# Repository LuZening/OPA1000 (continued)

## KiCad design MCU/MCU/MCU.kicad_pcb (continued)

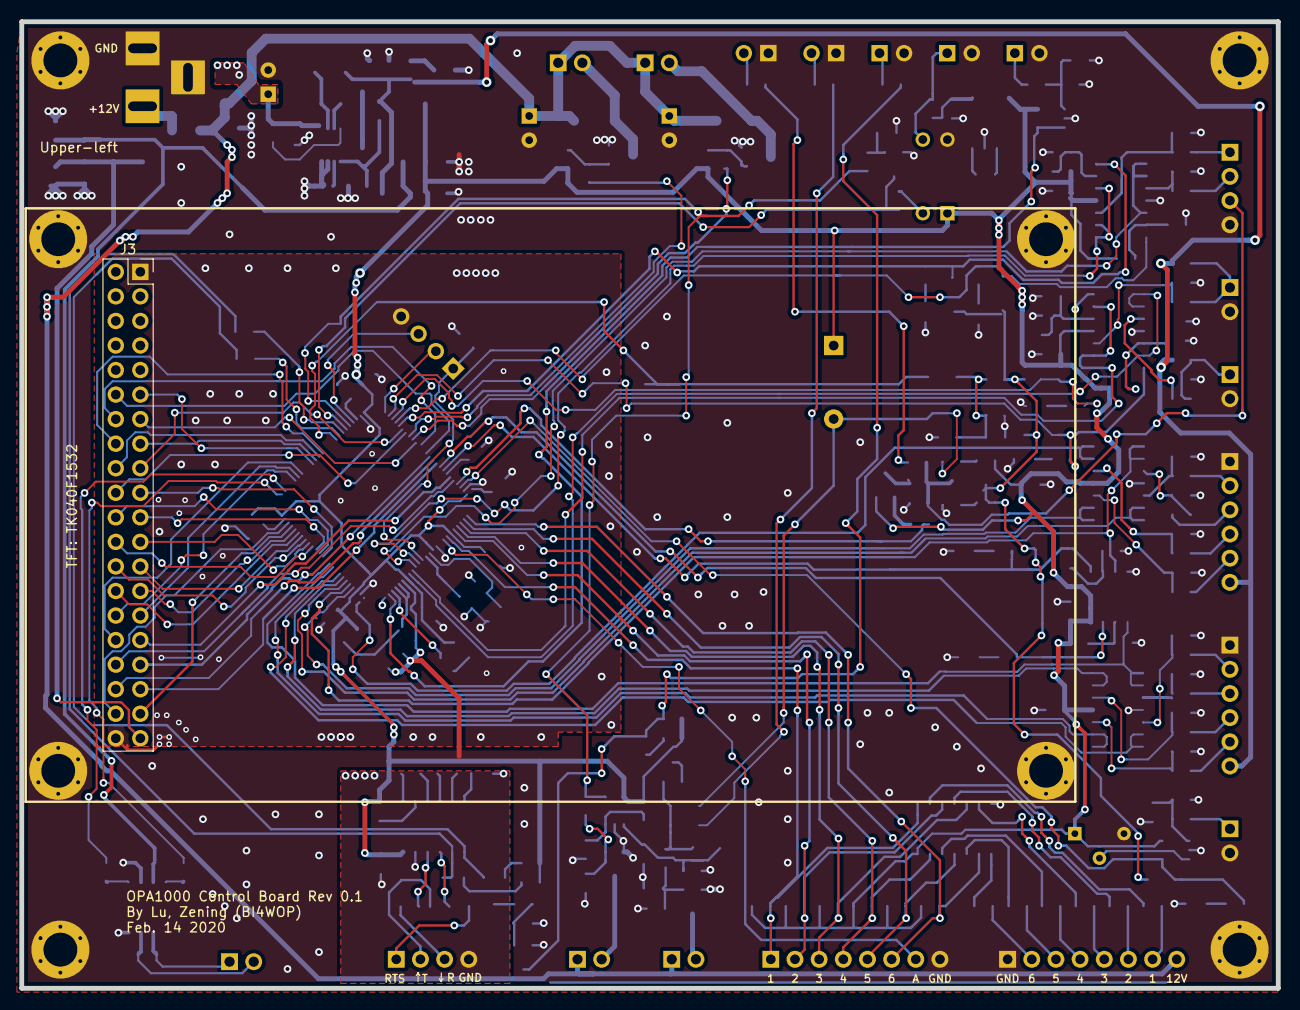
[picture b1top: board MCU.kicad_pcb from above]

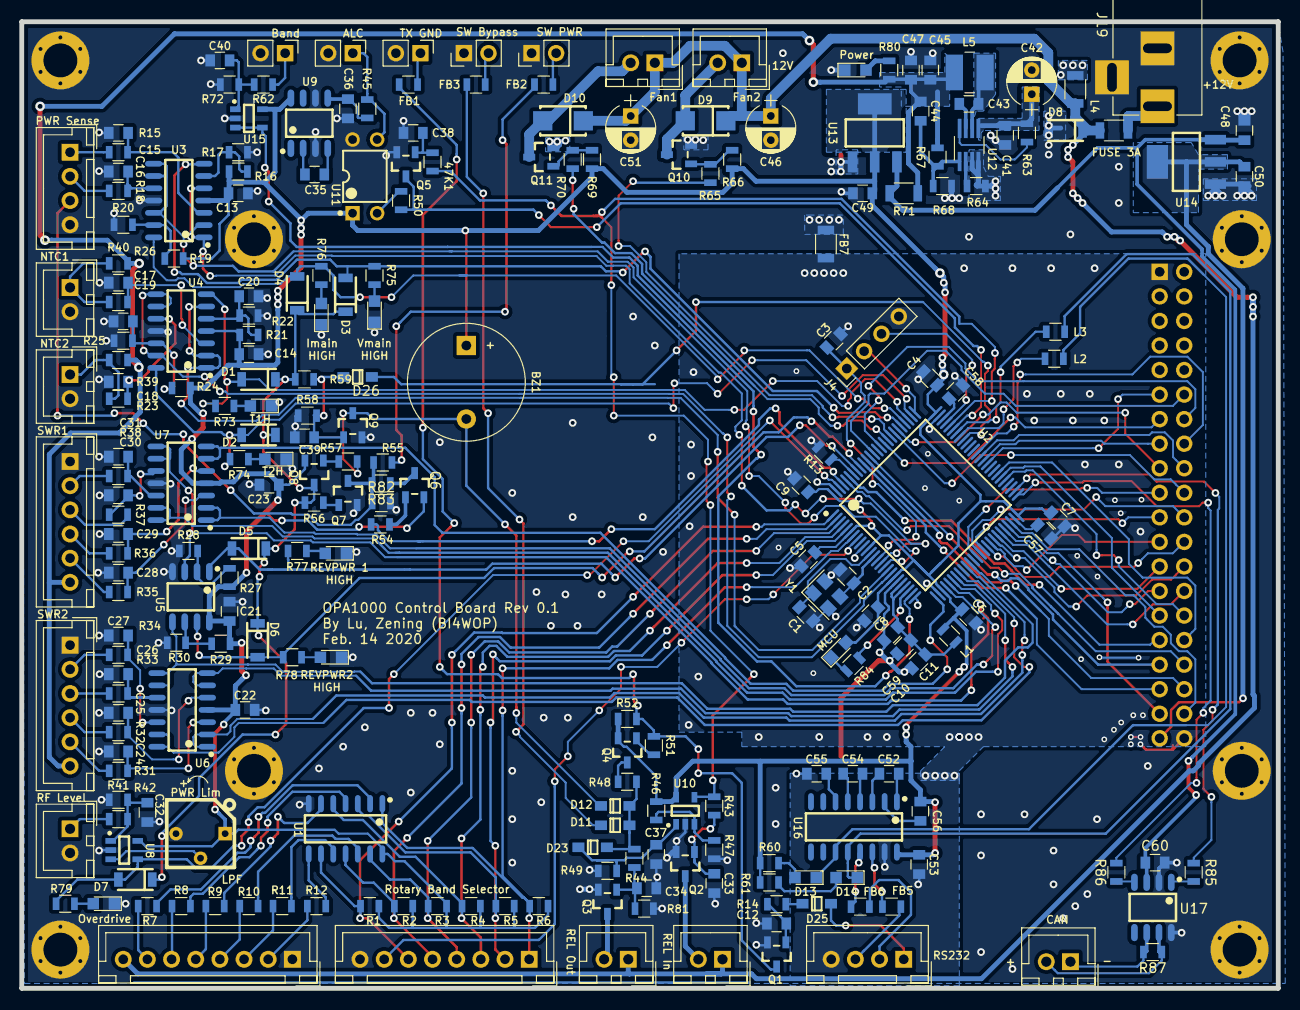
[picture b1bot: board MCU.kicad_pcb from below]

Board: 2 copper layers, 130.0 x 100.0 mm, 246 parts (237 on the bottom side), 199 nets.

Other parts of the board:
47K1: R_Small; R_0805
D26: SD103; SOD-123

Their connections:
/FaultHandling/Clear_Fault: D26.1; also elsewhere on the board
Clear_fault: D26.2; also elsewhere on the board
unnamed 86: 47K1.1; also elsewhere on the board
Transmit: 47K1.2; also elsewhere on the board

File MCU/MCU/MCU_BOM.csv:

"Comment","Description","Designator","Footprint","LibRef","Pins","Quantity","PartNumber","url",
"C_Small","desc","C34,C33,C23,C22,C21,C2,C1,","C_0805","libref","2","7","","",
"1nF","desc","C38,","C_0805","libref","2","1","","",
"102","desc","C39,","C_0805","libref","2","1","","",
"10nF NP0","desc","C43,","C_0805","libref","2","1","","",
"47pF","desc","C44,","C_0805","libref","2","1","","",
"10uF","desc","C50,C49,C45,C37,C36,C35,C11,","C_0805","libref","2","7","","",
"104","desc","C60,C59,C58,C57,C56,C55,C54,C53,C52,C48,C47,C41,C40,C32,C31,C30,C29,C28,C27,C26,C25,C24,C20,C19,C18,C17,C16,C15,C14,C13,C12,C10,C9,C8,C7,C6,C5,C4,C3,","C_0805","libref","2","39","","",
"SS14","desc","D10,D9,","SMA(DO-214AC)_S1","libref","2","2","","",
"T1H","desc","D15,","LED_0805","libref","2","1","","",
"T2H","desc","D16,","LED_0805","libref","2","1","","",
"VmH","desc","D17,","LED_0805","libref","2","1","","",
"ImH","desc","D18,","LED_0805","libref","2","1","","",
"R1H","desc","D19,","LED_0805","libref","2","1","","",
"R2H","desc","D20,","LED_0805","libref","2","1","","",
"OD","desc","D21,","LED_0805","libref","2","1","","",
"Power","desc","D22,","LED_0805","libref","2","1","","",
"LED","desc","D24,D14,D13,","LED_0805","libref","2","3","","",
"SD103","desc","D26,D25,D23,D12,D11,","SOD-123","libref","2","5","","",
"D","desc","D7,D6,D5,D4,D3,D2,D1,","LL-34","libref","2","7","","",
"16V","desc","D8,","LL-34","libref","2","1","","",
"2A","desc","F1,","R_1206","libref","2","1","","",
"1K","desc","FB6,FB5,FB3,FB2,FB1,R72,R61,R60,R58,R54,R44,R43,R41,R40,R39,R38,R37,R36,R35,R34,R33,R32,R31,R30,R29,R28,R27,R26,R25,R24,R23,R22,R21,R20,R19,R18,R17,R16,R15,","R_0805","libref","2","39","","",
"1K","desc","FB7,","R_1206","libref","2","1","","",
"600Ohm","desc","L3,L2,L1,","L_0805","libref","2","3","","",
"BEAD","desc","L4,","L_1206","libref","2","1","","",
"22uH","desc","L5,","L_SMD4030_hand","libref","2","1","","",
"AO3402","desc","Q11,Q10,","SOT-23(SOT-23-3)","libref","3","2","","",
"8550","desc","Q6,Q8,Q4,","SOT-23(SOT-23-3)","libref","3","3","","",
"8050","desc","Q9,Q7,Q5,Q3,Q2,Q1,","SOT-23(SOT-23-3)","libref","3","6","","",
"22K","desc","R42,","R_0805","libref","2","1","","",
"33k","desc","R46,","R_0805","libref","2","1","","",
"68K","desc","R47,","R_0805","libref","2","1","","",
"47K","desc","R51,","R_0805","libref","2","1","","",
"10","desc","R55,","R_0805","libref","2","1","","",
"3.3K","desc","R59,","R_0805","libref","2","1","","",
"100K","desc","R67,R64,R63,R57,R52,","R_0805","libref","2","5","","",
"16K","desc","R68,","R_0805","libref","2","1","","",
"0","desc","R71,","R_1206","libref","2","1","","",
"2.2K","desc","R80,R79,R78,R77,R76,R75,R74,R73,R50,","R_0805","libref","2","9","","",
"R_Small","desc","R81,47K1,","R_0805","libref","2","2","","",
"10K","desc","R83,R82,R69,R66,R56,R49,R48,R14,R6,R5,R4,R3,R2,R1,","R_0805","libref","2","14","","",
"4.7K","desc","R84,R45,R13,R12,R11,R10,R9,R8,R7,","R_0805","libref","2","9","","",
"100","desc","R86,R85,R70,R65,R62,","R_0805","libref","2","5","","",
"120","desc","R87,","R_0805","libref","2","1","","",
"74HC04","desc","U1,","SOIC-14_150MIL","libref","14","1","","",
"SY8303","desc","U12,","TSOT-23-8_HandSoldering","libref","8","1","","",
"AZ1117-3.3","desc","U14,U13,","SOT-223","libref","4","2","","",
"LMV321","desc","U15,U10,U8,","SOT-23-5","libref","5","3","","",
"MAX3232","desc","U16,","SOIC-16_150MIL","libref","16","1","","",
"TJA1042T","desc","U17,","SOIC-8_150MIL","libref","8","1","","",
"STM32F407VETx","desc","U2,","LQFP-100_14X14X05P","libref","100","1","","",
"LMV358","desc","U5,","SOIC-8_150MIL","libref","8","1","","",
"LMV324","desc","U6,U4,U7,U3,","SOIC-14_150MIL","libref","14","4","","",
"ICL7660","desc","U9,","SOIC-8_150MIL","libref","8","1","","",
"12MHz","desc","Y1,","Crystal_SMD_3225-4pin_3.2x2.5mm","libref","4","1","","",
"Through Hole Items ",
"Conn_02x20_Odd_Even","desc","J3,","Socket_Strip_Straight_2x20_Pitch2.54mm","libref","40","1","","",
"GND","desc","SC8,SC7,SC6,SC5,SC4,SC3,SC2,SC1,","M3_Screwhole","libref","7","8","","",
"Buzzer","desc","BZ1,","Buzzer_12x9.5RM7.6","libref","2","1","","",
"10u","desc","C42,","CP_Radial_D5.0mm_P2.50mm","libref","2","1","","",
"25V 47uF","desc","C51,C46,","CP_Radial_D5.0mm_P2.50mm","libref","2","2","","",
"Conn_01x02","desc","J11,J12,J10,J7,J6,","JST_XH_B02B-XH-A_02x2.50mm_Straight","libref","2","5","","",
"Conn_01x02","desc","J15,J13,J18,J16,J14,","Pin_Header_Straight_1x02_Pitch2.54mm","libref","2","5","","",
"Conn_01x04","desc","J17,J5,","JST_XH_B04B-XH-A_04x2.50mm_Straight","libref","4","2","","",
"Barrel_Jack_Switch","desc","J19,","BARREL_JACK","libref","3","1","","",
"Conn_01x08","desc","J2,J1,","JST_XH_B08B-XH-A_08x2.50mm_Straight","libref","8","2","","",
"CAN","desc","J20,","JST_XH_B02B-XH-A_02x2.50mm_Straight","libref","2","1","","",
"Conn_01x04","desc","J4,","Pin_Header_Straight_1x04_Pitch2.54mm","libref","4","1","","",
"Conn_01x06","desc","J9,J8,","JST_XH_B06B-XH-A_06x2.50mm_Straight","libref","6","2","","",
"Fan","desc","M2,M1,","JST_XH_B02B-XH-A_02x2.50mm_Straight","libref","2","2","","",
"10K","desc","RV1,","3362P","libref","3","1","","",
"PC817","desc","U11,","DIP-4","libref","4","1","","",

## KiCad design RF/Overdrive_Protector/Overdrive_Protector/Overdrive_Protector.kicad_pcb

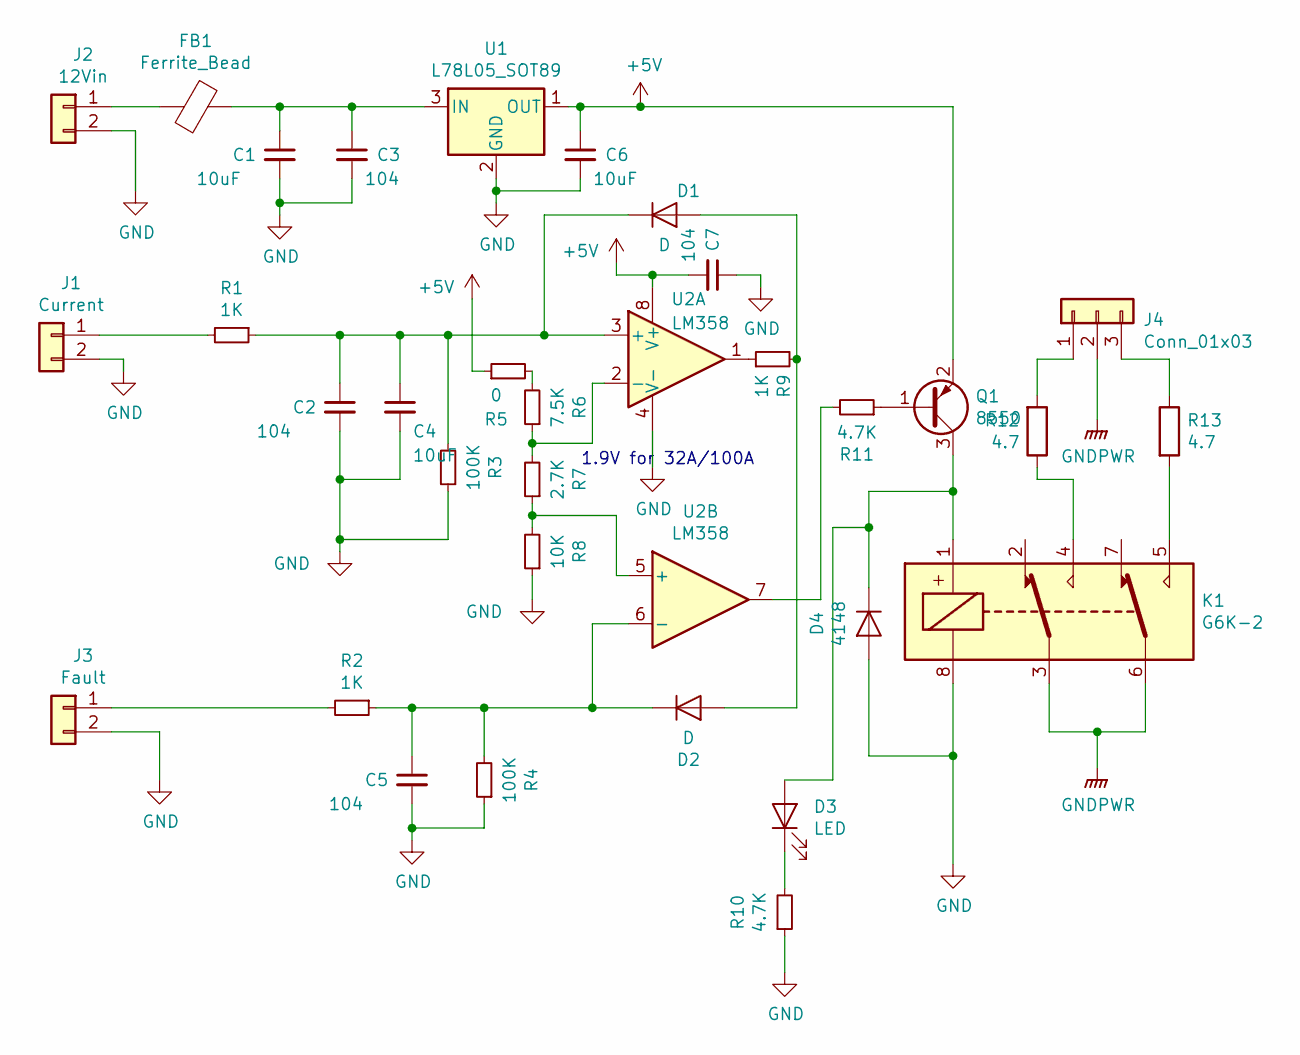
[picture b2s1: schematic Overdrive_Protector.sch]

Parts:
C1, C4, C6: 10uF; 1206_C
C2, C3, C5, C7: 104; 0805_C
D1, D2: D; SOD-123
D3: LED; LED_0805_HandSoldering
D4: 4148; SOD-123
FB1: Ferrite_Bead; 1206_L
J1: Current; JST_PH_S2B-PH-SM4-TB_02x2.00mm_Angled
J2: 12Vin; JST_PH_S2B-PH-SM4-TB_02x2.00mm_Angled
J3: Fault; JST_PH_S2B-PH-SM4-TB_02x2.00mm_Angled
J4: Conn_01x03; JST_PH_S3B-PH-SM4-TB_03x2.00mm_Angled
K1: G6K-2; HFD4S
Q1: 8550; SOT-23(SOT-23-3)
R1, R2, R9: 1K; 0805_R
R3, R4: 100K; 0805_R
R5: 0; 0805_R
R6: 7.5K; 0805_R
R7: 2.7K; 0805_R
R8: 10K; 0805_R
R10, R11: 4.7K; 0805_R
R12, R13: 4.7; 1206_R
U1: L78L05_SOT89; SOT-89(SOT-89-3)
U2: LM358; SOIC-8_150MIL

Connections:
+5V: C6.1, C7.2, Q1.2 (E), R5.1, U1.1 (OUT), U2.8 (V+)
GND: C1.2, C2.2, C3.2, C4.2, C5.2, C6.2, C7.1, D4.1 (A), J1.2, J2.2, J3.2, K1.8, R3.1, R4.1, R8.1, R10.1, U1.2 (GND), U2.4 (V-)
GNDPWR: J4.2, K1.3, K1.6
unnamed: C1.1, C3.1, FB1.1, U1.3 (IN)
unnamed: C2.1, C4.1, D1.2 (K), R1.1, R3.2, U2.3 (+)
unnamed: C5.1, D2.2 (K), R2.1, R4.2, U2.6 (-)
unnamed: D1.1 (A), D2.1 (A), R9.2
unnamed: D3.1 (K), R10.2
unnamed: D3.2 (A), D4.2 (K), K1.1, Q1.3 (C)
unnamed: FB1.2, J2.1
unnamed: J1.1, R1.2
unnamed: J3.1, R2.2
unnamed: J4.1, R12.2
unnamed: J4.3, R13.1
unnamed: K1.4, R12.1
unnamed: K1.5, R13.2
unnamed: Q1.1 (B), R11.1
unnamed: R5.2, R6.2
unnamed: R6.1, R7.2, U2.2 (-)
unnamed: R7.1, R8.2, U2.5 (+)
unnamed: R9.1, U2.1
unnamed: R11.2, U2.7

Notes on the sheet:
1.9V for 32A/100A

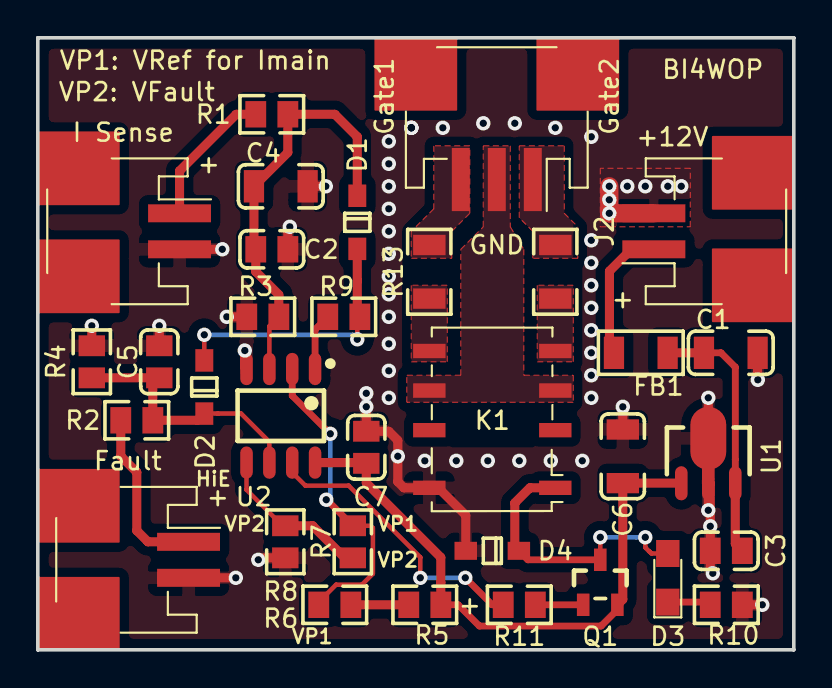
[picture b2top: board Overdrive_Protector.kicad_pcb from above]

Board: 2 copper layers, 42.0 x 34.0 mm, 33 parts (0 on the bottom side), 22 nets.

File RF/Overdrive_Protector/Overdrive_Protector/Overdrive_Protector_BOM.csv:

"Comment","Description","Designator","Footprint","LibRef","Pins","Quantity","PartNumber","url",
"10uF","desc","C6,C4,C1,","1206_C","libref","2","3","","",
"104","desc","C7,C5,C3,C2,","0805_C","libref","2","4","","",
"D","desc","D2,D1,","SOD-123","libref","2","2","","",
"LED","desc","D3,","LED_0805_HandSoldering","libref","2","1","","",
"4148","desc","D4,","SOD-123","libref","2","1","","",
"Ferrite_Bead","desc","FB1,","1206_L","libref","2","1","","",
"Current","desc","J1,","JST_PH_S2B-PH-SM4-TB_02x2.00mm_Angled","libref","4","1","","",
"Vin","desc","J2,","JST_PH_S2B-PH-SM4-TB_02x2.00mm_Angled","libref","4","1","","",
"Fault","desc","J3,","JST_PH_S2B-PH-SM4-TB_02x2.00mm_Angled","libref","4","1","","",
"Conn_01x03","desc","J4,","JST_PH_S3B-PH-SM4-TB_03x2.00mm_Angled","libref","5","1","","",
"G6K-2","desc","K1,","HFD4S","libref","8","1","","",
"8550","desc","Q1,","SOT-23(SOT-23-3)","libref","3","1","","",
"4.7K","desc","R10,R11,","0805_R","libref","2","2","","",
"4.7","desc","R13,R12,","1206_R","libref","2","2","","",
"100K","desc","R4,R3,","0805_R","libref","2","2","","",
"200","desc","R5,","0805_R","libref","2","1","","",
"7.2K","desc","R6,","0805_R","libref","2","1","","",
"2.6K","desc","R7,","0805_R","libref","2","1","","",
"10K","desc","R8,","0805_R","libref","2","1","","",
"1K","desc","R9,R2,R1,","0805_R","libref","2","3","","",
"L78L05_SOT89","desc","U1,","SOT-89(SOT-89-3)","libref","4","1","","",
"LM358","desc","U2,","SOIC-8_150MIL","libref","8","1","","",

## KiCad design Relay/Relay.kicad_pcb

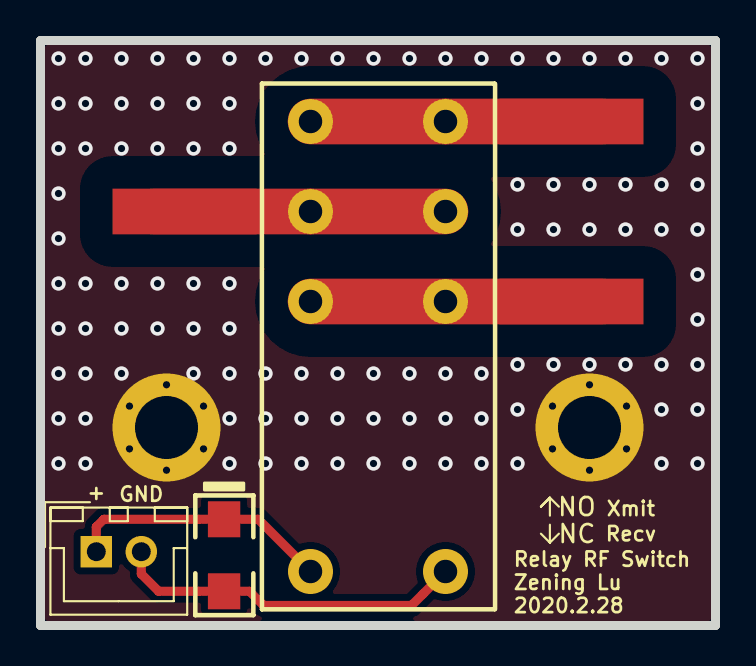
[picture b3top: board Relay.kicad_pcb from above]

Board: 2 copper layers, 37.5 x 32.5 mm, 8 parts (0 on the bottom side), 6 nets.

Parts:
D1: 1N4007; SMAF_S4
J1, J2, J3: Conn_Coaxial; RF_strip
J4: Conn_01x02; JST_XH_B02B-XH-A_02x2.50mm_Straight
K1: G2RL-1-E
SC1, SC2: Conn_01x01; M3_Screwhole

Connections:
+12V: D1.2, J4.1, K1.1
Earth: SC1.1, SC2.1
GND: D1.1, J4.2, K1.8
unnamed: J1.1, K1.3, K1.6
unnamed: J2.1, K1.2, K1.7
unnamed: J3.1, K1.4, K1.5

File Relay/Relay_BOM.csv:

"Comment","Description","Designator","Footprint","LibRef","Pins","Quantity","PartNumber","url",
"1N4007","desc","D1,","SMAF_S4","libref","2","1","","",
"Conn_Coaxial","desc","J3,J2,J1,","RF_strip","libref","1","3","","",
"Through Hole Items ",
"Conn_01x02","desc","J4,","JST_XH_B02B-XH-A_02x2.50mm_Straight","libref","2","1","","",
"G2RL-1-E","desc","K1,","G2RL-1-E","libref","8","1","","",
"Conn_01x01","desc","SC2,SC1,","M3_Screwhole","libref","7","2","","",
